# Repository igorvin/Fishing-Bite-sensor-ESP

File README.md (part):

# 🎣 Fishing Bite Sensor

[Русская версия](README_RU.md)

**A wireless bite alarm for fishing rods.** A small sensor on the rod notices even weak line pulls, signals locally with LEDs and a buzzer, and reports the bite over ESP-NOW radio to a **hub**: a receiver with a screen and a vibration motor that stays next to you. No router, Internet or app is needed; all settings open in your phone's browser.

> **Project status.** This is a bench release: the firmware is covered by tests and has run on real XIAO ESP32-C3 boards (sensor + hub), but it **has not been tried on real fishing trips yet**. Bite-detection accuracy, radio range and battery life have not been measured.

## Contents

- [Features](#features)
- [What you need](#what-you-need)
- [Wiring](#wiring)
- [Installing the firmware](#installing-the-firmware)
- [Pairing the sensor with the hub](#pairing-the-sensor-with-the-hub)
- [Web interface](#web-interface)
- [Using it on the water](#using-it-on-the-water)
- [Button, sleep and wake](#button-sleep-and-wake)
- [Signals and states](#signals-and-states)
- [Hub](#hub)
- [Tuning sensitivity](#tuning-sensitivity)
- [Battery](#battery)
- [Troubleshooting](#troubleshooting)
- [For developers](#for-developers)

## Features

**Rod sensor**

- 🎯 **Sensitive detection.** The LSM6DS3 accelerometer is read 104 times per second. The *Dynamic XYZ* algorithm removes gravity and reacts to a jolt in any direction, including across the rod.
- 🔇 **Wind protection.** The sensor reacts to the **sharp** jolt of a bite and ignores the smooth vibration wind gives the rod. The wind level is tracked continuously over the last 10 seconds, so a gust does not raise a false alarm and full sensitivity comes back in calm.
- 🎣 **Pause while handling the rod.** When you pick up or tilt the rod, alarms pause. Once the rod is still again in its **new** position, the sensor re-arms by itself.
- 🔔 **Local signals.** Whenever the sensor is awake (armed or not) the red LED gives a short flash every 5 seconds, so you can tell it from deep sleep, where everything is dark. While armed the green LED is also on. A bite is red LED plus buzzer. Volume is adjustable.
- 📡 **ESP-NOW radio to the hub.** Three events: first bite, continuing bite, low battery.
- 📱 **A simple web page.** The sensor runs its own Wi-Fi access point with a page at `http://192.168.4.1`: state, arming, sensitivity (5 steps), volume. Everything else is in the *Settings* menu.
- 🔘 **One button** for arming, disarming, deep sleep and wake.
- 🔋 **Battery saving.** The sensor sleeps on a button hold or by itself after 3 idle minutes. A brush against the button in a bag does not wake it. Below 3.30 V it also goes to sleep to protect the cell.
- 💾 **Settings are kept** in flash and survive firmware updates.
- 🧾 **Event journal.** The sensor records what it decided and why: button presses, calibrations, arming. Read it over USB with `log`.

**Hub (receiver)**

- 🖥️ 128×64 OLED with a Cyrillic font: the name of the rod that has a bite, in large letters.
- 📳 Vibration motor with different patterns for a bite, a continuing bite and a sensor's low battery.
- 🎣 Up to 8 sensors per hub, log of the last 12 events.
- 🌙 The start-up screen (with the hub MAC) stays on for 20 seconds, then turns off and wakes only for a new alert.
- 🔘 Button: hold 1.5 s to show the hub MAC for pairing, short press for the status screen.

## What you need

| Device | Parts | Notes |
|---|---|---|
| **Sensor** | Seeed XIAO ESP32-C3 (bench) or XIAO ESP32-S3 (PCB v4), LSM6DS3 module (I²C), green and red LEDs, passive buzzer (through a transistor), momentary push button, 3.7 V Li-ion cell, 100 kΩ / 100 kΩ battery divider | A KiCad v4.1 board and an 18650 enclosure are in [`kicad/kicad_bite`](kicad/kicad_bite) |
| **Hub** | XIAO ESP32-C3 or S3, SH1106 128×64 OLED (I²C), vibration motor through a MOSFET, push button, LED, Li-ion cell, 100 kΩ / 100 kΩ divider | Separate firmware in [`ESP_HUB/`](ESP_HUB). Circuit and parts: [docs/hub-hardware.md](docs/hub-hardware.md) (Russian) |
| **Phone** | Any smartphone with Wi-Fi and a browser | Only for configuration |
| **Computer** | [PlatformIO](https://platformio.org/install), USB-C cable | For flashing |

<p align="center">
  
  <br><em>Concept: the sensor in a compact case, strapped to the rod with hook-and-loop straps.</em>
</p>

<p align="center">

  <br><em>PCB v4.1 and the sealed tube enclosure for an 18650 cell (design files; not yet built or tested).</em>
</p>

## Wiring

### Sensor — bench (XIAO ESP32-C3 / S3)

| Signal | XIAO pin | Notes |
|---|---|---|
| Button | **D1** | To GND; internal pull-up |
| Battery (100k/100k divider) | D2 | |
| LSM6DS3 SDA / SCL | D4 / D5 | Module powered from 3.3 V |
| Green LED | D7 | Through a resistor or driver |
| Red LED | D8 | Through a resistor or driver |
| Passive buzzer | D9 | Through a transistor; 3 kHz PWM |

The button must be on **D1**: the board cannot wake from deep sleep on D6. D0 and D6 are unused by the current firmware.

### Sensor — Waveshare ESP32-S3-Zero (environment `s3_zero`)

This board labels its pins by GPIO number (GP1…GP13), not D0…D10, so the wiring is given in GPIO numbers:

| Signal | GPIO | Notes |
|---|---|---|
| LSM6DS3 SDA / SCL | GP4 / GP5 | Module powered from 3.3 V |
| Button (to GND) | GP6 | Wakes from deep sleep; internal pull-up |
| Battery (100k/100k divider) | GP7 | |
| Green LED | GP8 | |
| Red LED | GP9 | |
| Passive buzzer (through a transistor) | GP10 | 3 kHz PWM |

Do not use GP0 (BOOT button), GP3 (affects boot), GP21 (on-board RGB LED), GP19/GP20 (USB) or TX/RX (GP43/GP44). **The ESP32-S3-Zero has no battery charger or BAT pads:** connect a Li-ion cell through a separate charge/protection module to the 5V pin and take the divider from the cell. Check against Waveshare's schematic for your board revision: the pinout above is verified by building the firmware only, not on the board itself.

### Sensor — PCB v4 (XIAO ESP32-S3, environment `bite_v4_s3`)

Button D1 (external 10k pull-up), battery D0, red LED D8, green LED D9, buzzer D10, LSM6DS3 on D4/D5.

### Hub

| Signal | XIAO pin | Waveshare ESP32-S3-Zero (`s3_zero`) |
|---|---|---|
| OLED SDA / SCL | D4 / D5 | GP4 / GP5 |
| LED | D1 | GP8 |
| Motor MOSFET | D2 | GP9 |
| Button (to GND) | D3 | GP6 |
| Battery (100k/100k divider) | A0 | GP7 |

Choosing and wiring the vibration motor, with the parts list: [docs/hub-hardware.md](docs/hub-hardware.md) (Russian). In short: an AO3400A MOSFET with 100 Ω gate resistor and 100 kΩ gate pull-down, an SS14 flyback diode across the motor, 10 µF + 100 nF on the motor supply, motor powered from 3V3.

> ⚠️ Drive the motor and any loud buzzer through a transistor, never straight from a pin. Connect the Li-ion cell to the XIAO **BAT+ / BAT−** pads, not to 3V3. Power details: [docs/power-and-wiring.md](docs/power-and-wiring.md).

## Installing the firmware

1. **Install PlatformIO**, either [PlatformIO IDE for VS Code](https://platformio.org/install/ide?install=vscode) or the [PlatformIO Core CLI](https://docs.platformio.org/en/latest/core/installation/index.html). Make sure `pio --version` works.

2. **Get the project.**

   ```bash
   git clone https://github.com/igorvin/Fishing-Bite-sensor-ESP.git
   ```

   ```bash
   cd Fishing-Bite-sensor-ESP
   ```

3. **Flash the sensor.** Connect the sensor board over USB and pick the environment for your board. `<PORT>` is the board's port, e.g. `/dev/ttyACM0` or `COM5`.

   | Board | Environment |
   |---|---|
   | XIAO ESP32-C3 (bench) | `xiao_esp32c3` |
   | XIAO ESP32-S3 (bench) | `seeed_xiao_esp32s3` |
   | PCB v4 (XIAO ESP32-S3) | `bite_v4_s3` |
   | Waveshare ESP32-S3-Zero | `s3_zero` |

   ```bash
   pio run -e xiao_esp32c3 -t upload --upload-port <PORT>
   ```

4. **Flash the hub.** Connect the **other** board, the hub, and run:

   ```bash
   pio run -d ESP_HUB -e xiao_esp32c3 -t upload --upload-port <PORT>
   ```

   For a XIAO ESP32-S3 use `-e seeed_xiao_esp32s3`, for a Waveshare ESP32-S3-Zero `-e s3_zero`.

> 💡 Mind the ports: hub firmware on the sensor (or the other way round) will not work. For an ordinary update **do not** run `erase_flash` or `uploadfs`; they wipe the saved settings.

## Pairing the sensor with the hub

The sensor sends events only to the hub whose MAC address you give it.

1. **Find the hub's MAC.** It is on the bottom line of the start-up screen for 20 seconds after the hub is switched on. Holding the hub button for 1.5 seconds shows it in large digits for 30 seconds. Over USB: type `mac` in the hub's serial monitor.

   ```bash
   pio device monitor -d ESP_HUB --port <PORT> --baud 115200
   ```

2. **Give the MAC to the sensor**, in either of two ways:
   - **From the phone:** open the *Settings* menu, type the MAC into "Hub MAC" and press **"Save and restart"**. A filled-in MAC turns the hub link on by itself.
   - **Over USB:** in the sensor's serial monitor type `peer AA:BB:CC:DD:EE:FF` (the sensor must be disarmed).

3. **Check the link.** After the restart the sensor introduces itself to the hub. The sensor's page shows "Answered at power-on" in the Hub row, and the `status` command in the hub's serial monitor shows `rods=1`. Start-up order does not matter: if you restart the hub, a running sensor registers again.

> ℹ️ Registration is a one-off hello at start-up, not a continuous link check. Individual bites are not acknowledged. Before fishing, check that an alarm reaches the hub: arm the sensor and tap the rod.

## Web interface

1. Power on the sensor (or wake it by holding the button for about 1 s).
2. On your phone join the Wi-Fi network **`BiteSensor`** (the name on first start; no password).
3. Open **http://192.168.4.1** in the browser.

Everything fits on one page; the rarely used fields are in the **Settings** menu. Changes are saved at once; when something goes wrong (for example an ARM is cancelled) a pop-up message appears.

<table>
<tr>
<td align="center" width="50%"><br><b>Main page</b></td>
<td align="center" width="50%"><br><b>Settings</b></td>
</tr>
</table>

<sub>Pictures are taken from the firmware's real web front end (Settings library 1.4.3) with example values.</sub>

### Main page

| Item | What it shows or does |
|---|---|
| **State** | Off / Arming… / ARMED / Paused: rod is being moved / Calibrating… / Sensor error |
| **Battery** | Approximate charge in percent; "no reading" on USB power only |
| **Hub** | "Not set up" (enter its MAC) / "Waiting for the hub" / "Answered at power-on" / "Radio error" |
| **Armed** | Arms or disarms, like the button |
| **Sensitivity** | 5 steps, "High" by default (see below) |
| **Volume** | Buzzer volume, 0–100 % |
| **Test signal** | A short buzzer and red-LED signal. Nothing is sent to the hub |

| Sensitivity | Sharpness floor | Threshold in wind |
|---|---|---|
| Low | 0.030 g | wind level × 10 |
| Below medium | 0.022 g | × 8 |
| Medium | 0.016 g | × 7 |
| **High** (default) | 0.012 g | × 6 |
| Very high | 0.009 g | × 5 |

### Settings menu

| Setting | Description |
|---|---|
| **Rod name** | The sensor's Wi-Fi name and the name on the hub screen; the hub shows the first 16 bytes (16 Latin letters). Give each sensor its own name, e.g. "Feeder", "Carp-1" |
| **Wi-Fi password** | Empty (open) or 8–63 characters |
| **Hub MAC** | The hub's MAC as `AA:BB:CC:DD:EE:FF`. Empty means the hub link is off |
| **Save and restart** | Applies the three fields above. They have no effect until you press it |
| **Language / Язык** | English or Русский |

Everything else (signal timings, the movement pause with its 25° / 35° limits, LED brightness 100 %) runs on tested defaults. Technical data, the journal and raw capture are available over USB (see [USB commands](#troubleshooting)).

## Using it on the water

1. **Power on or wake the sensor.** Hold the button for about 1 second until it beeps. The sensor measures the background straight away, so **keep it still for 2 seconds**.
2. **Mount the sensor on the rod** and put the rod on its rest.
3. **Arm.** Hold the button for 1–3 seconds: a short beep sounds at 1 second, then release. The **green LED blinks** while the sensor checks for 1.5 seconds that it is *steady* (*SETTLING*): swaying in wind is fine, being handled or moved is not and restarts the check. When the green LED stays on and a **long beep** sounds, it is armed. Do not press again while green is blinking: a second press disarms. If the sensor has not been calibrated yet, it starts calibrating 1 second after you release the button (do not touch it for 2 seconds).
4. **Bite:** red LED and buzzer on the sensor, screen and vibration on the hub. The signal repeats while the line keeps moving.
5. **Picked up the rod?** No need to disarm: the sensor pauses alarms and re-arms by itself once the rod is still again, in its new position.
6. **Disarm** with the same 1–3 second hold: the green LED goes out and you hear a short beep.
7. **Sleep.** Hold the button for more than 3 seconds (long beep) and release. A disarmed sensor with nobody connected also falls asleep after 3 minutes.

> 💡 While armed, the sensor's Wi-Fi stays on for 2 more minutes and then switches off to save power. To open the settings again, disarm with the button; the access point comes back.

## Button, sleep and wake

| Action | Result |
|---|---|
| Hold 1–3 s and release | Short beep at 1 s; on release the sensor arms or disarms. If not calibrated, calibration starts 1 s after release |
| Hold ≥ 3 s and release | Long beep at 3 s; on release it disarms, saves settings and sleeps |
| Touch < 1 s while asleep | Nothing: it goes straight back to sleep (protection against presses in a bag) |
| Hold ≈ 1 s while asleep | Beep, wake, calibration, DISARMED. The sensor registers with the hub again |
| 3 min disarmed with no presses or connections | Sleep |
| Battery < 3.30 V (three readings in a row) | If armed, the hub gets "low battery"; then the sensor sleeps |

## Signals and states

| Situation | Green | Red | Buzzer | Hub |
|---|---|---|---|---|
| Awake, disarmed | — | short flash every 5 s | short beep when disarming | — |
| Arming (SETTLING) | blinking | short flash every 5 s | — | — |
| Armed | on | short flash every 5 s | long beep when ARMED is reached | — |
| Deep sleep | — | — | — | — |
| **ARM cancelled**: the sensor moved during calibration | — | 3 flashes | 3 short beeps | — |
| Bite (event 1) | on | flash | short signal | screen + 300 ms vibration |
| Continuing bite (event 2) | on | repeated flashes | repeated signals | 800 ms vibration at the start of the episode |
| Rod being moved (pause) | — | — | silent | — |
| Battery ≤ 20 % while armed (event 3) | | | | screen + 2 short vibrations |
| Holding the button | | | beep at 1 s, long beep at 3 s | |

```mermaid
stateDiagram-v2
    direction LR
    state "Calibrating" as Cal
    state "Disarmed" as Off
    state "Settling" as Settle
    state "Armed" as Armed
    state "Suppressed (moving)" as Pause
    state "IMU fault" as Fault
    [*] --> Cal: power on
    Cal --> Off: 2 s still
    Off --> Settle: ARM
    Settle --> Armed: 1.5 s still
    Armed --> Armed: bite → signal
    Armed --> Pause: rod tilted
    Pause --> Settle: still again
    Armed --> Off: DISARM
    Pause --> Off: DISARM
    Armed --> Fault: accelerometer lost
    Fault --> Cal: accelerometer back
```

An accelerometer fault or a manual disarm **never** re-arms the sensor by itself; you arm it again yourself.

## Hub

After power-on the hub shows for about 20 seconds how many sensors it has seen, its own battery and, on the bottom line, **its MAC address** for pairing; then the screen turns off. A new bite or battery warning turns on the screen and the motor.

<table>
<tr>
<td align="center"><br>Ready to receive</td>
<td align="center"><br>Bite on rod "ФИДЕР"</td>
</tr>
<tr>
<td align="center"><br>Sensor battery low</td>
<td align="center"><br>Event log (USB command)</td>
</tr>
</table>

<sub>Frames are produced by the hub's own drawing code (`ESP_HUB/tools/render_preview.py`) with example names. The hub's interface is in Russian.</sub>

**Hub button (D3):** hold 1.5 s for the hub MAC (30 seconds); short press for the status screen (another short press turns the screen off). Alerts always take priority.

- Rod numbers (01, 02, …) follow the order in which sensors first appear after the hub starts. After a hub restart the list and log start empty.
- List, log and service screens open with serial commands: `summary`, `list`, `history`, `service`, `mac`, `status`, `help`. `motor` runs the motor for 300 ms as a wiring test.
- More: [ESP_HUB/README.md](ESP_HUB/README.md), [docs/hub-testing.md](docs/hub-testing.md).

## Tuning sensitivity

1. Start with **High**.
2. Arm and tap the rod blank lightly or pull the line. If nothing happens, choose **Very high**.
3. Leave the rod on its rest for a few minutes, ideally in the wind. If false alarms appear, go one step lower.
4. The current threshold and wind level are shown over USB: `status` (`ambient`, `threshold`) and the journal line `ARMED: ambient … -> threshold …`.

### Wind and a swaying rod

Wind recordings (`docs/field-analysis-2026-11-24.md`) showed the wind shaking the rod about 5 times a second by ±0.2–0.3 g, while a bite is a short sharp jolt ringing at 15–30 Hz. So the sensor looks at **sharpness**: a filter removes everything slower than ~12 Hz, and the floor and multiplier come from the sensitivity step. The background level is the median sharpness over the last ~10 seconds (excluding the latest second), refreshed every half second in every state.

On the same recordings, through the firmware core, at "High": in strong wind the sensor arms and stays armed with no false alarm, catches 33 of 35 light simulated bites in calm and 19 of 24 taps in wind. Before: 35 false alarms a minute and 12 of 35.

Arming does not need complete stillness. A 1.5 s window is checked for **steadiness**:

| Check | Limit | Means |
|---|---|---|
| Position drift (first vs second half of the window) | 0.035 g (≈2°) | the rod is being moved to a new place |
| Peak-to-peak jolt on any axis | 0.20 g; in strong sway up to 6 × sway, never above 0.80 g | the sensor is being handled |
| Sway (standard deviation) | 0.15 g | wind too strong |

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
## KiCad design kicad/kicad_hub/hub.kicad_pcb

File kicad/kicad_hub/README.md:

# Плата и корпус хаба (плата rev A, корпус rev B; черновик, 2026-11-27)

Плата 68 × 40 мм под XIAO ESP32-C3, модуль OLED SH1106 1,3″, вибромотор, кнопку и тонкий LiPo 703048 (48 × 30 × 7 мм, ~1000 мА·ч) с быстрой зарядкой BQ24074. Корпус «бипер» 72 × 44 × 19 мм со скруглёнными углами и рёбрами и откидной клипсой: сложенная держит хаб на ремне, откинутая служит подставкой на столе (с клипсой толщина ~24 мм).

Корпус rev B (2026-11-27, по просьбе сделать тоньше и эстетичнее): был 75 × 47 × 24 (30 с клипсой) под LiPo 10 мм. Тоньше за счёт аккумулятора 7 мм вместо 10, зазора над ним 1 мм вместо 2, гребёнки OLED 3,0 мм вместо 3,5 и более тонких крышки и лицевой стенки. Угловые винты убраны, поэтому углы скруглены R ≈ 3,7 мм в плане, лицевое ребро R 3, заднее R 1,2. Плата не менялась.

**Статус:** проект собран генератором и проверен программно (нетлист, DRC, проверка посадки в корпусе). Ничего не заказано и не собрано. Перед заказом надо сверить с даташитами пункты из раздела «Проверить до заказа».

| | |
|---|---|
|  |  |
|  |  |

## Файлы

| Файл | Что это |
|---|---|
| `hub.kicad_sch`, `hub_schematic.pdf`, `docs/img/schematic-1.png` | схема (формат KiCad 7, открывается в KiCad 8/9) |
| `hub.kicad_pcb` | разведённая плата, 2 слоя, 1,0 мм, заливка GND с обеих сторон |
| `hub.pretty`, `hub.kicad_sym` | свои посадочные места (XIAO, OLED на гребёнке, площадки мотора) и символ XIAO ESP32-C3 |
| `fab/hub_gerbers.zip` | Gerber + сверловка для заказа платы |
| `fab/hub-bom.csv`, `fab/hub-pos.csv` | перечень деталей и координаты для монтажа |
| `fab/hub.step` | 3D-модель платы (детали без моделей — только площадки) |
| `docs/drc_report.txt` | DRC: 0 ошибок, 0 неразведённых; 2 предупреждения — шёлкография библиотечного SW1 выходит за край (так задумано: рычажок свешивается) |
| `enclosure/hub_enclosure.scad` | параметрическая модель корпуса (OpenSCAD), размеры в начале файла |
| `enclosure/stl/*.stl` | детали для печати |
| `_generator/` | генератор: схема → плата → Freerouting → заливка → DRC → файлы производства |

## Схема

Питание: **USB-C J1 → F1/VD1 → BQ24074 → SYS → выключатель SW1 → диод D3 → вывод 5V XIAO → стабилизатор XIAO 3,3 В** → OLED, мотор, светодиод.

- **Зарядка BQ24074:** ток заряда ≈ 0,59 А (R3 = 1,5 кОм, ≈ 0,6C для 703048 ~1000 мА·ч, полная зарядка ≈ 2–2,5 ч; если паспорт аккумулятора разрешает меньше, увеличить R3), входной ток ≈ 1 А (R4 = 1,5 кОм). Power-path: от USB хаб работает и во время зарядки. TS — резистор 10 кОм вместо NTC (температура аккумулятора не контролируется). Светодиоды: красный D1 «заряжается», зелёный D2 «USB подключён», видны через глухие окна в корпусе.
- **USB-C J1** — только питание (CC1/CC2 через 5,1 кОм), данных нет. Прошивка — через USB-C самой XIAO на верхнем торце.
- **Аккумулятор** — разъём JST-PH 2P J2 снизу платы. Q1 (AO3401A) защищает от разъёма с обратной полярностью (у китайских LiPo она встречается). **Аккумулятор должен быть со своей платой защиты**: отдельной защиты от переразряда на плате нет.
- **SW1** разрывает питание XIAO, зарядка работает и при выключенном хабе. **D3** не даёт USB XIAO питать зарядник в обратную сторону, поэтому оба USB можно подключать одновременно (проверить на первом образце).
- **Выводы как в прошивке `ESP_HUB`** (ничего менять не нужно): светодиод D1, мотор D2 (AO3400A, диод D4, 10 мкФ + 100 нФ), кнопка D3 к GND, OLED D4/D5 (подтяжки 4,7 кОм), делитель батареи 100k/100k на A0.

## Корпус

| Деталь | Материал / печать |
|---|---|
| `shell.stl` — оболочка с экраном | **полупрозрачный (натуральный) или белый PETG**: светодиоды светят через глухие окна 0,6 мм. Печать экраном вниз |
| `cover.stl` — задняя крышка с рамкой аккумулятора, кольцом мотора и петлями клипсы | PETG, наружной стороной вниз |
| `clip.stl` — клипса/подставка | PETG (гнётся без излома), на боку |
| `pusher.stl` — толкатель кнопки | PETG |
| `flap.stl` — заглушка USB-C зарядки и выключателя | **ТПУ 85–95A** |
| `plug_top.stl` — пробка USB-C XIAO | ТПУ |
| `gasket.stl` — плоская прокладка крышки 0,8 мм | ТПУ 85A |

Защита от воды «от дождя и брызг»: прокладка по шву крышки, толкатель кнопки с O-кольцом 2,5 × 1,0 в отверстии Ø4,1, окно экрана — пластина 34,6 × 20,6 × 1 мм (акрил или поликарбонат) вклеена изнутри на силикон, светодиоды без отверстий, оба USB-C под ТПУ-заглушками. Погружение не предусмотрено.

Клипса крепится винтом M2 × 40–45 (или отрезком прутка 2 мм) через три петли с самоконтрящейся гайкой: затяжкой регулируется, насколько туго она откидывается. Сложенная, она оставляет под ремень зазор 3,0 мм с зацепом на конце. Откинутая примерно на 42°, она упирается выступом в крышку и держит хаб на столе.

Сборка: четыре самореза M2 × 14 вставляются сзади через крышку, её стойки и крепёжные отверстия платы и вкручиваются в бобышки оболочки (пилот Ø1,8). Так одни винты держат и плату, и крышку, а углы свободны для скругления. Аккумулятор лежит в рамке крышки между рядами стоек; над ним до платы 1 мм, поэтому выводы THT-деталей снизу платы обрезать заподлицо и проложить каптон.

## Предположения (уточнить, сейчас не измерено)

1. **LiPo 703048: 48 × 30 × 7 мм, ~1000 мА·ч** (размеры по типовой маркировке, с платой защиты и выводами JST-PH). Вариант тоньше — 603048 (6 мм, ~850 мА·ч, корпус 18 мм). Размер задаётся параметром `BAT` в `.scad`; ширина больше 30 мм не пройдёт между стойками винтов.
2. **Модуль OLED 1,3″ 35,4 × 33,5 мм, выводы GND-VCC-SCL-SDA** на верхнем краю. Бывают модули с VCC и GND наоборот — тогда плату нужно поменять (или резать дорожки). Окно `WIN` 31 × 17 мм по центру модуля — сверить с реальным стеклом.
3. Модуль OLED стоит над платой на гребёнке с зазором 3,0 мм; детали под ним не выше 1,0 мм.
4. Ток хаба не измерен; ~1000 мА·ч по оценке хватит на 12–15 ч.

## Проверить до заказа

- BQ24074: формулы ISET/ILIM (K_ISET = 890, K_ILIM = 1550 взяты по памяти), назначение вывода 15 (SYSOFF у BQ24074; R6 0 Ом на GND, при необходимости не ставить), таймер TMR оставлен свободным.
- Посадочное место XIAO (`hub:XIAO_THT`) — по чертежу Seeed: 14 площадок, шаг 2,54, ряды 15,24 мм.
- Полярность разъёма аккумулятора: 1 = «+» (по маркировке на нижнем слое).
- Ориентация JST J2 и SW1 на реальных деталях, вылет рычажка SW1 за край платы (~1 мм).

## Пересборка

```sh
# Linux (Ubuntu 24.04): apt install kicad kicad-symbols kicad-footprints openscad xvfb
bash kicad/kicad_hub/_generator/run_hub.sh        # схема, плата, трассировка, DRC, Gerber, BOM (~3 мин)
bash kicad/kicad_hub/enclosure/build.sh           # STL, картинки, проверка посадки (~1 мин)
```

На macOS с KiCad 8/9 задать `KPY` и `KICAD_CLI` (см. начало `run_hub.sh`). Freerouting 2.1 скачивается сам. Трассировщик не детерминирован: скрипт повторяет трассировку, пока DRC не покажет 0 неразведённых площадок, поэтому дорожки при каждой пересборке немного разные.

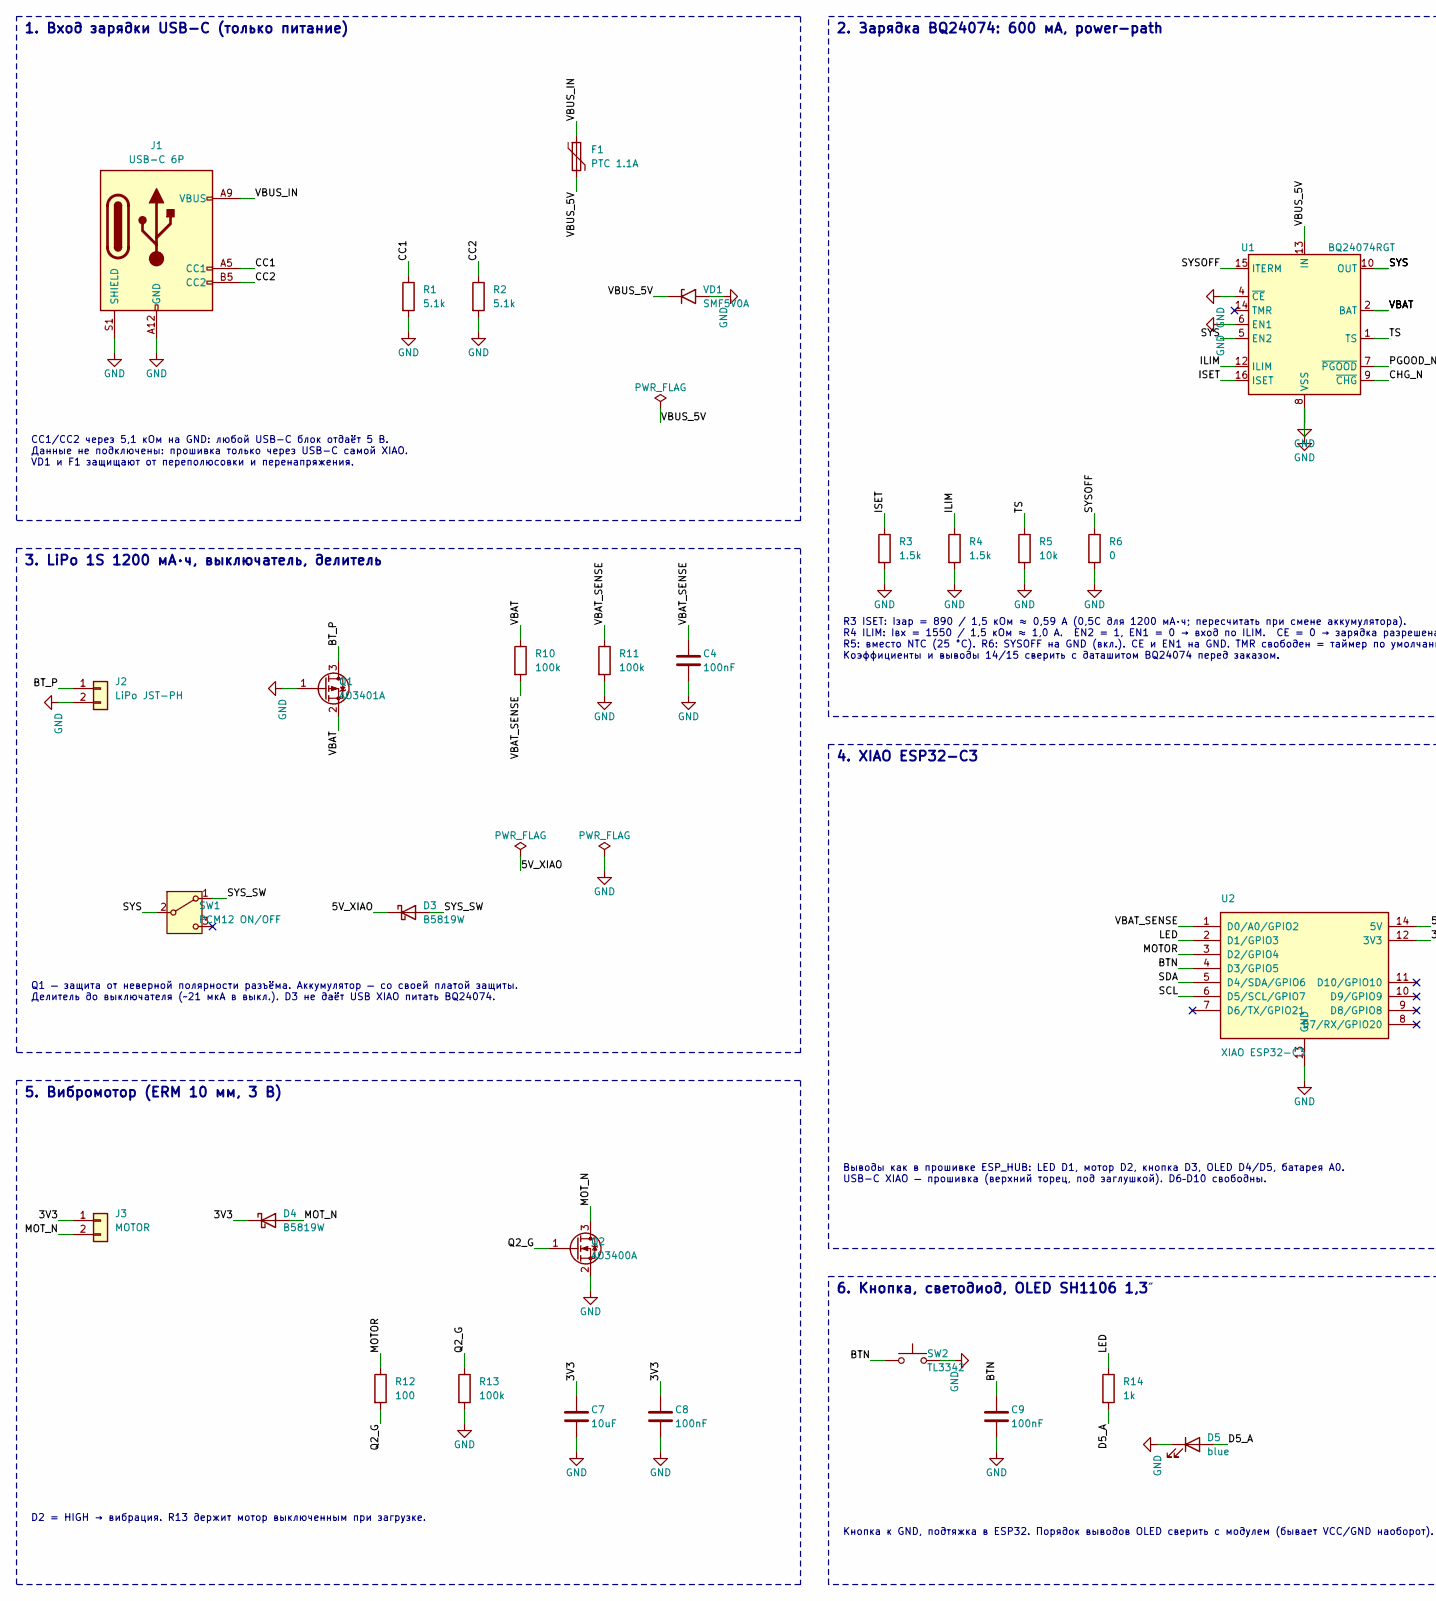
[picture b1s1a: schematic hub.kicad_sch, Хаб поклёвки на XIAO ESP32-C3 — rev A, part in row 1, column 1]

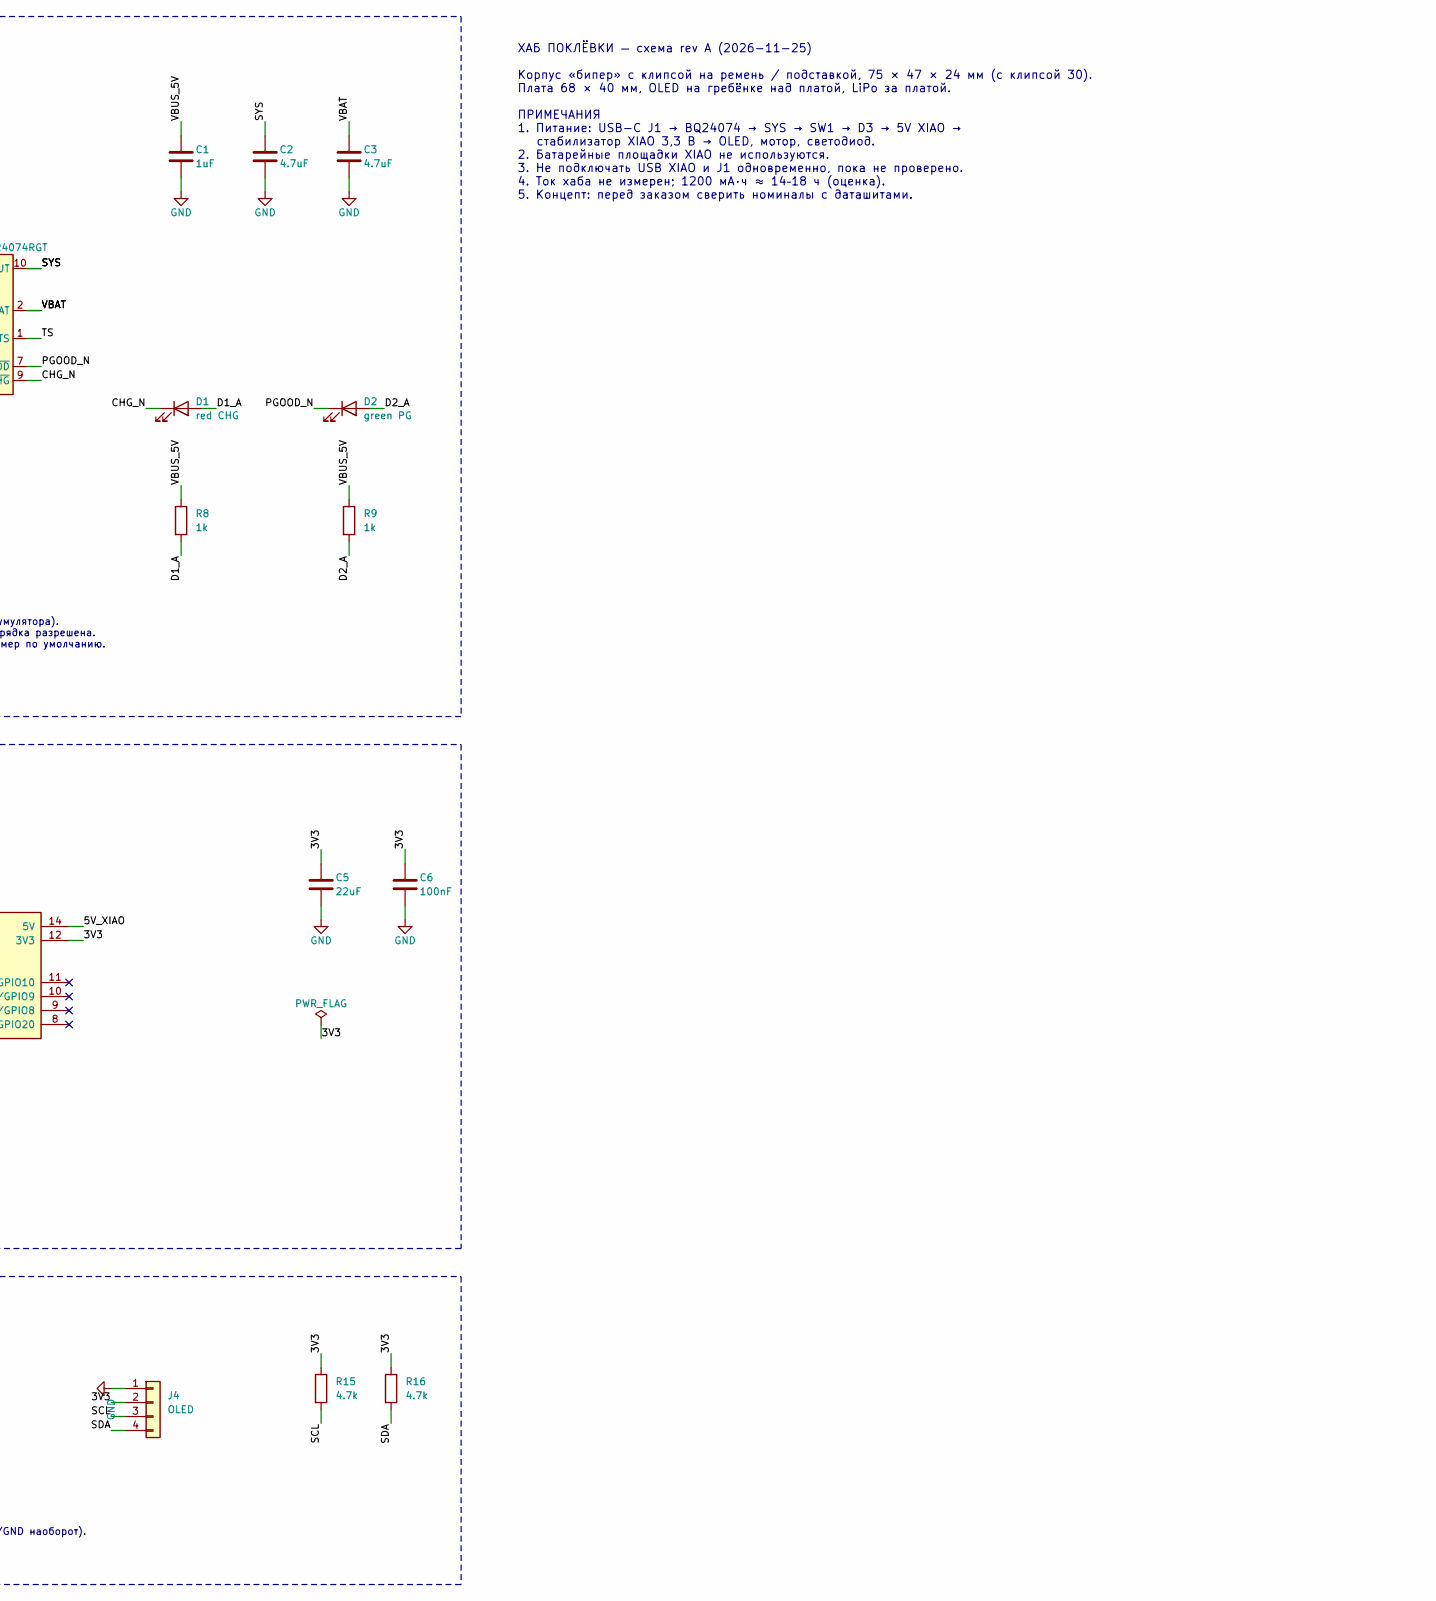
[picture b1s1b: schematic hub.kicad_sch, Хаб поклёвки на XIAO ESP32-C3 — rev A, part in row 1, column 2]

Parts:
C1: 1uF; C_0805_2012Metric
C2, C3: 4.7uF; C_0805_2012Metric
C4, C6, C8, C9: 100nF; C_0603_1608Metric
C5: 22uF; C_0805_2012Metric
C7: 10uF; C_0805_2012Metric
D1: red CHG; LED_0603_1608Metric
D2: green PG; LED_0603_1608Metric
D3, D4: B5819W; D_SOD-123
D5: blue; LED_0603_1608Metric
F1: PTC 1.1A; Fuse_1206_3216Metric; MPN Bourns MF-NSMF110-2
J1: USB-C 6P; USB_C_Receptacle_GCT_USB4125-xx-x-0190_6P_TopMnt_Horizontal; MPN GCT USB4125-GF-A-0190
J2: LiPo JST-PH; JST_PH_S2B-PH-SM4-TB_1x02-1MP_P2.00mm_Horizontal; MPN JST S2B-PH-SM4-TB
J3: MOTOR; WIRE_2P
J4: OLED; PinHeader_1x04_P2.54mm_Vertical
Q1: AO3401A; SOT-23
Q2: AO3400A; SOT-23
R1, R2: 5.1k; R_0603_1608Metric
R3, R4: 1.5k; R_0603_1608Metric
R5: 10k; R_0603_1608Metric
R6: 0; R_0603_1608Metric
R8, R9, R14: 1k; R_0603_1608Metric
R10, R11, R13: 100k; R_0603_1608Metric
R12: 100; R_0603_1608Metric
R15, R16: 4.7k; R_0603_1608Metric
SW1: PCM12 ON/OFF; SW_SPDT_PCM12; MPN C&K PCM12SMTR
SW2: TL3342; SW_SPST_TL3342; MPN E-Switch TL3342F160QG
U1: BQ24074RGT; VQFN-16-1EP_3x3mm_P0.5mm_EP1.6x1.6mm; MPN TI BQ24074RGTR
U2: XIAO ESP32-C3; XIAO_THT; MPN Seeed 113991054
VD1: SMF5V0A; D_SMF

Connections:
/3V3: C5.1, C6.1, C7.1, C8.1, D4.1 (K), J3.1, J4.2, R15.1, R16.1, U2.12 (3V3)
/5V_XIAO: D3.1 (K), U2.14 (5V)
/BTN: C9.1, SW2.1, U2.4 (D3/GPIO5)
/BT_P: J2.1, Q1.3 (D)
/CC1: J1.A5 (CC1), R1.1
/CC2: J1.B5 (CC2), R2.1
/CHG_N: D1.1 (K), U1.9 (~CHG)
/D1_A: D1.2 (A), R8.2
/D2_A: D2.2 (A), R9.2
/D5_A: D5.2 (A), R14.2
/ILIM: R4.1, U1.12 (ILIM)
/ISET: R3.1, U1.16 (ISET)
/LED: R14.1, U2.2 (D1/GPIO3)
/MOTOR: R12.1, U2.3 (D2/GPIO4)
/MOT_N: D4.2 (A), J3.2, Q2.3 (D)
/PGOOD_N: D2.1 (K), U1.7 (~PGOOD)
/Q2_G: Q2.1 (G), R12.2, R13.1
/SCL: J4.3, R15.2, U2.6 (D5/SCL/GPIO7)
/SDA: J4.4, R16.2, U2.5 (D4/SDA/GPIO6)
/SYS: C2.1, SW1.2 (B), U1.5 (EN2), U1.10 (OUT), U1.11 (OUT)
/SYSOFF: R6.1, U1.15 (ITERM)
/SYS_SW: D3.2 (A), SW1.1 (A)
/TS: R5.1, U1.1 (TS)
/VBAT: C3.1, Q1.2 (S), R10.1, U1.2 (BAT), U1.3 (BAT)
/VBAT_SENSE: C4.1, R10.2, R11.1, U2.1 (D0/A0/GPIO2)
/VBUS_5V: C1.1, F1.2, R8.1, R9.1, U1.13 (IN), VD1.1 (A1)
/VBUS_IN: F1.1, J1.A9 (VBUS), J1.B9 (VBUS)
GND: C1.2, C2.2, C3.2, C4.2, C5.2, C6.2, C7.2, C8.2, C9.2, D5.1 (K), J1.A12 (GND), J1.B12 (GND), J1.S1 (SHIELD), J2.2, J4.1, Q1.1 (G), Q2.2 (S), R1.2, R2.2, R3.2, R4.2, R5.2, R6.2, R11.2, R13.2, SW2.2, U1.4 (~CE), U1.6 (EN1), U1.8 (VSS), U1.17 (VSS), U2.13 (GND), VD1.2 (A2)

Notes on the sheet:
1. Вход зарядки USB-C (только питание)
CC1/CC2 через 5,1 кОм на GND: любой USB-C блок отдаёт 5 В. Данные не подключены: прошивка только через USB-C самой XIAO. VD1 и F1 защищают от переполюсовки и перенапряжения.
2. Зарядка BQ24074: 600 мА, power-path
R3 ISET: Iзар = 890 / 1,5 кОм ≈ 0,59 А (0,5C для 1200 мА·ч; пересчитать при смене аккумулятора). R4 ILIM: Iвх = 1550 / 1,5 кОм ≈ 1,0 А. EN2 = 1, EN1 = 0 → вход по ILIM. CE = 0 → зарядка разрешена. R5: вместо NTC (25 °C). R6: SYSOFF на GND (вкл.). CE и EN1 на GND. TMR свободен = таймер по умолчанию.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
3. LiPo 1S 1200 мА·ч, выключатель, делитель
Q1 — защита от неверной полярности разъёма. Аккумулятор — со своей платой защиты. Делитель до выключателя (~21 мкА в выкл.). D3 не даёт USB XIAO питать BQ24074.
4. XIAO ESP32-C3
Выводы как в прошивке ESP_HUB: LED D1, мотор D2, кнопка D3, OLED D4/D5, батарея A0. USB-C XIAO — прошивка (верхний торец, под заглушкой). D6–D10 свободны.
5. Вибромотор (ERM 10 мм, 3 В)
D2 = HIGH → вибрация. R13 держит мотор выключенным при загрузке.
6. Кнопка, светодиод, OLED SH1106 1,3″
Кнопка к GND, подтяжка в ESP32. Порядок выводов OLED сверить с модулем (бывает VCC/GND наоборот).
ХАБ ПОКЛЁВКИ — схема rev A (2026-11-25) Корпус «бипер» с клипсой на ремень / подставкой, 75 × 47 × 24 мм (с клипсой 30). Плата 68 × 40 мм, OLED на гребёнке над платой, LiPo за платой. ПРИМЕЧАНИЯ 1. Питание: USB-C J1 → BQ24074 → SYS → SW1 → D3 → 5V XIAO → стабилизатор XIAO 3,3 В → OLED, мотор, свето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

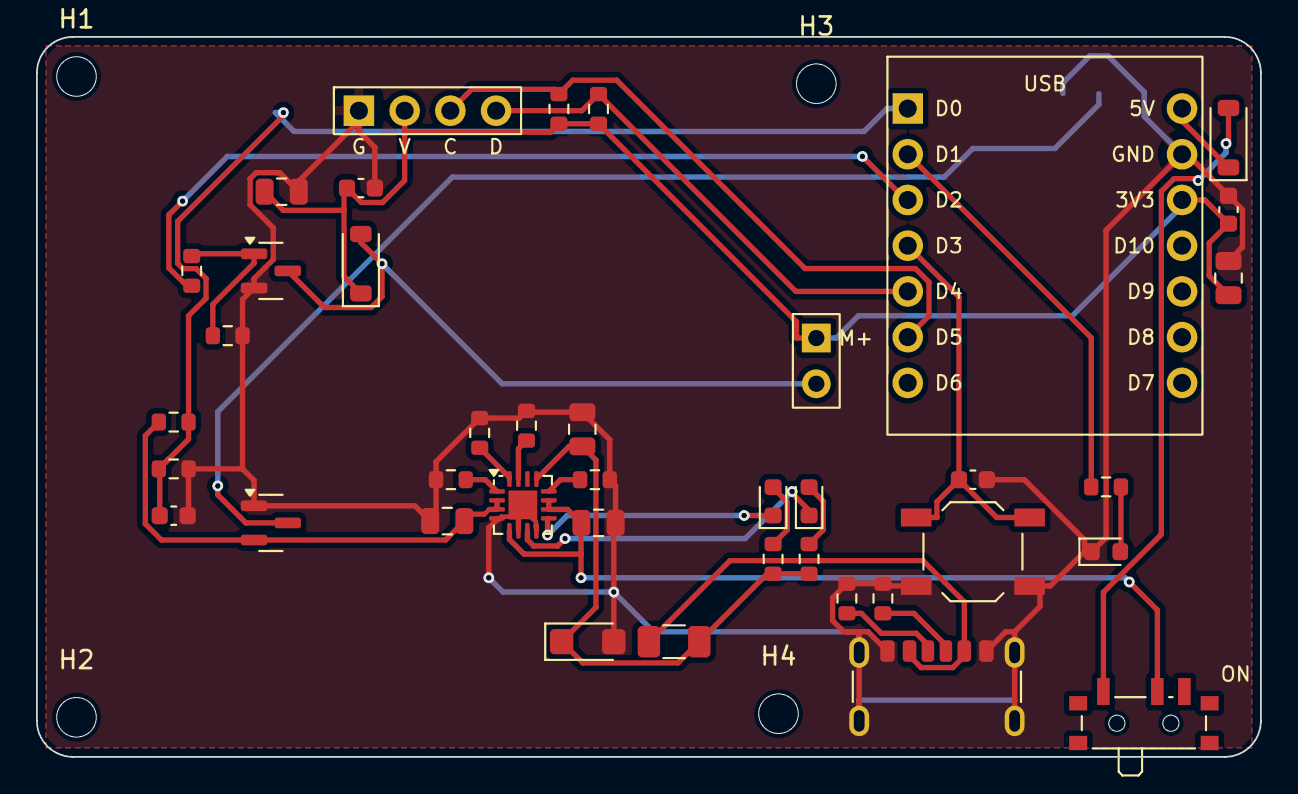
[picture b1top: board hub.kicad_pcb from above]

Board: 2 copper layers, 68.0 x 40.0 mm, 45 parts (1 on the bottom side), 28 nets.

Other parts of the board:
H1, H2, H3, H4: MountingHole_2.2mm_M2

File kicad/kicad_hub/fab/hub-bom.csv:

Qty,References,Value,Footprint,MPN / note
1,C1,1uF,C_0805_2012Metric,
2,C2 C3,4.7uF,C_0805_2012Metric,
4,C4 C6 C8 C9,100nF,C_0603_1608Metric,
1,C5,22uF,C_0805_2012Metric,
1,C7,10uF,C_0805_2012Metric,
1,D1,red CHG,LED_0603_1608Metric,
1,D2,green PG,LED_0603_1608Metric,
2,D3 D4,B5819W,D_SOD-123,
1,D5,blue,LED_0603_1608Metric,
1,F1,PTC 1.1A,Fuse_1206_3216Metric,Bourns MF-NSMF110-2
1,J1,USB-C 6P,USB_C_Receptacle_GCT_USB4125-xx-x-0190_6P_TopMnt_Horizontal,GCT USB4125-GF-A-0190
1,J2,LiPo JST-PH,JST_PH_S2B-PH-SM4-TB_1x02-1MP_P2.00mm_Horizontal,JST S2B-PH-SM4-TB
1,J3,MOTOR,WIRE_2P,
1,J4,OLED,PinHeader_1x04_P2.54mm_Vertical,
1,Q1,AO3401A,SOT-23,
1,Q2,AO3400A,SOT-23,
2,R1 R2,5.1k,R_0603_1608Metric,
2,R3 R4,1.5k,R_0603_1608Metric,
1,R5,10k,R_0603_1608Metric,
1,R6,0,R_0603_1608Metric,
3,R8 R9 R14,1k,R_0603_1608Metric,
3,R10 R11 R13,100k,R_0603_1608Metric,
1,R12,100,R_0603_1608Metric,
2,R15 R16,4.7k,R_0603_1608Metric,
1,SW1,PCM12 ON/OFF,SW_SPDT_PCM12,C&K PCM12SMTR
1,SW2,TL3342,SW_SPST_TL3342,E-Switch TL3342F160QG
1,U1,BQ24074RGT,VQFN-16-1EP_3x3mm_P0.5mm_EP1.6x1.6mm,TI BQ24074RGTR
1,U2,XIAO ESP32-C3,XIAO_THT,Seeed 113991054
1,VD1,SMF5V0A,D_SMF,

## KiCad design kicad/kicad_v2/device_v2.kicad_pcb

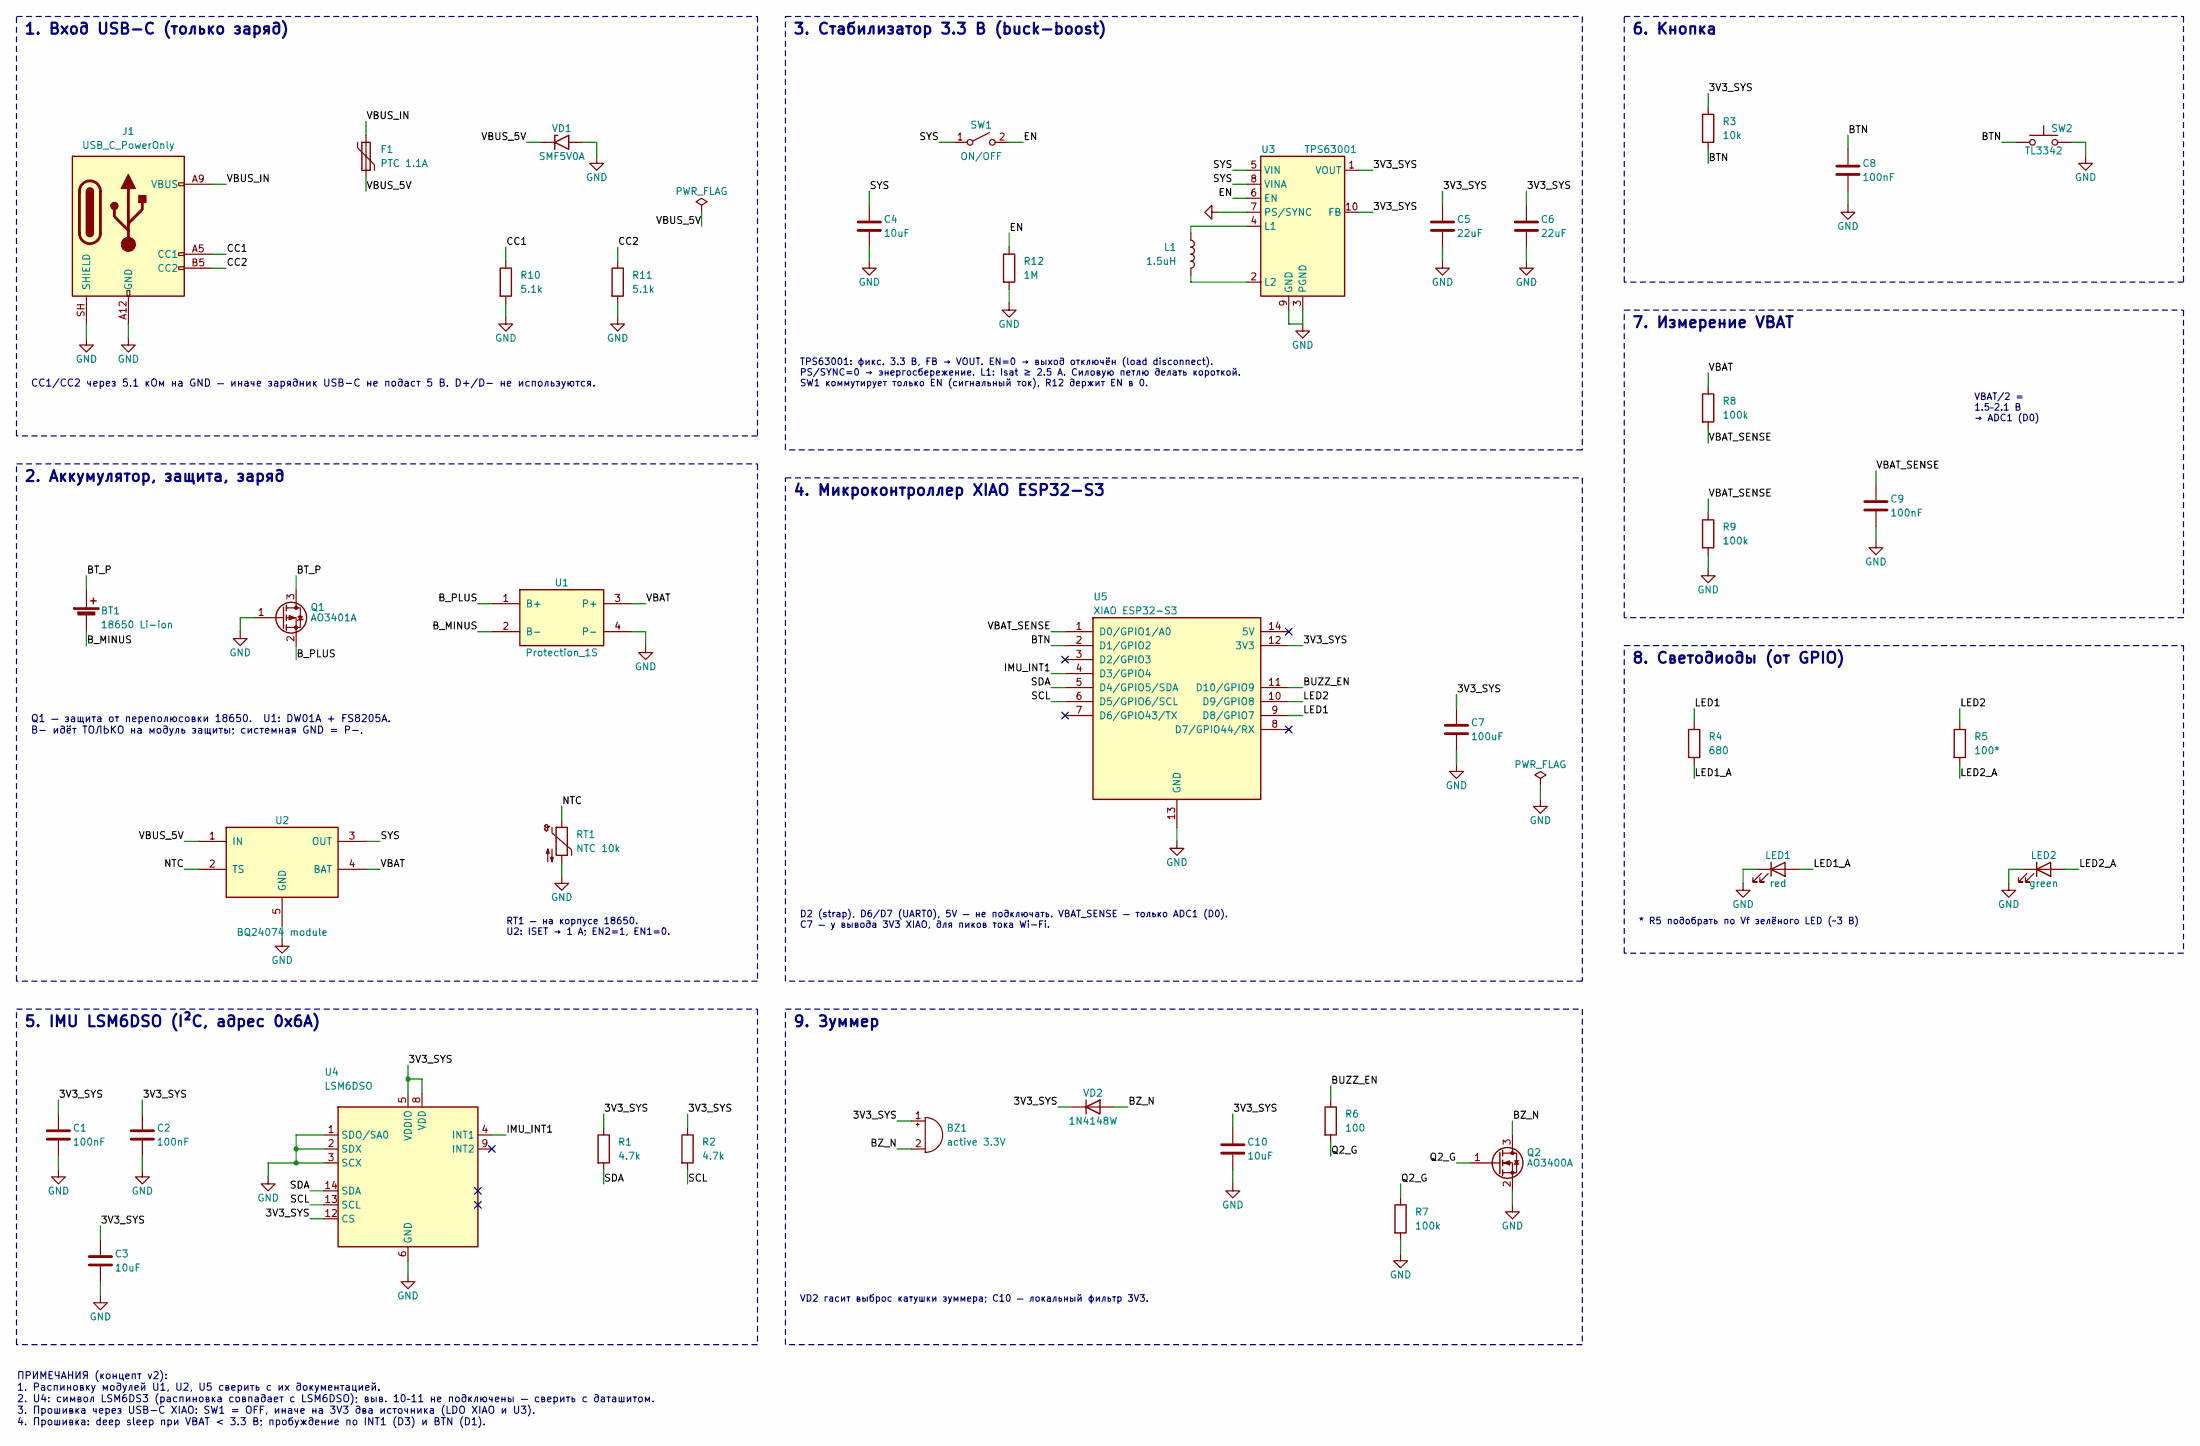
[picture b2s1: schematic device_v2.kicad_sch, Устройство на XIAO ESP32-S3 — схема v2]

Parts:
BT1: 18650 Li-ion; BatteryHolder_Keystone_1042_1x18650
BZ1: active 3.3V; Buzzer_12x9.5RM7.6
C1, C2, C8, C9: 100nF; C_0603_1608Metric
C3, C4, C10: 10uF; C_0805_2012Metric
C5, C6: 22uF; C_0805_2012Metric
C7: 100uF; C_1206_3216Metric
F1: PTC 1.1A; Fuse_1206_3216Metric
J1: USB_C_PowerOnly; USB_C_Receptacle_GCT_USB4125-xx-x_6P_TopMnt_Horizontal
L1: 1.5uH; L_Bourns-SRN4018
LED1: red; LED_0603_1608Metric
LED2: green; LED_0603_1608Metric
Q1: AO3401A; SOT-23
Q2: AO3400A; SOT-23
R1, R2: 4.7k; R_0603_1608Metric
R3: 10k; R_0603_1608Metric
R4: 680; R_0603_1608Metric
R5: 100*; R_0603_1608Metric
R6: 100; R_0603_1608Metric
R7, R8, R9: 100k; R_0603_1608Metric
R10, R11: 5.1k; R_0603_1608Metric
R12: 1M; R_0603_1608Metric
RT1: NTC 10k; NTC_WIRE_2P
SW1: ON/OFF; SW_SPDT_PCM12
SW2: TL3342; SW_SPST_TL3342
U1: Protection_1S; PROT_1S_HDR4
U2: BQ24074 module; BQ24074_MODULE_HDR5
U3: TPS63001; Texas_DRC0010J
U4: LSM6DSO; LGA-14_3x2.5mm_P0.5mm_LayoutBorder3x4y
U5: XIAO ESP32-S3; XIAO_ESP32S3_THT
VD1: SMF5V0A; D_SMF
VD2: 1N4148W; D_SOD-123

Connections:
/3V3_SYS: BZ1.1 (+), C1.1, C2.1, C3.1, C5.1, C6.1, C7.1, C10.1, R1.1, R2.1, R3.1, U3.1 (VOUT), U3.10 (FB), U4.5 (VDDIO), U4.8 (VDD), U4.12 (CS), U5.12 (3V3), VD2.1 (K)
/BTN: C8.1, R3.2, SW2.1, U5.2 (D1/GPIO2)
/BT_P: BT1.1 (+), Q1.3 (D)
/BUZZ_EN: R6.1, U5.11 (D10/GPIO9)
/BZ_N: BZ1.2 (-), Q2.3 (D), VD2.2 (A)
/B_MINUS: BT1.2 (-), U1.2 (B-)
/B_PLUS: Q1.2 (S), U1.1 (B+)
/CC1: J1.A5 (CC1), R10.1
/CC2: J1.B5 (CC2), R11.1
/EN: R12.1, SW1.2 (B), U3.6 (EN)
/IMU_INT1: U4.4 (INT1), U5.4 (D3/GPIO4)
/LED1: R4.1, U5.9 (D8/GPIO7)
/LED1_A: LED1.2 (A), R4.2
/LED2: R5.1, U5.10 (D9/GPIO8)
/LED2_A: LED2.2 (A), R5.2
/NTC: RT1.1, U2.2 (TS)
/Q2_G: Q2.1 (G), R6.2, R7.1
/SCL: R2.2, U4.13 (SCL), U5.6 (D5/GPIO6/SCL)
/SDA: R1.2, U4.14 (SDA), U5.5 (D4/GPIO5/SDA)
/SYS: C4.1, SW1.1 (A), U2.3 (OUT), U3.5 (VIN), U3.8 (VINA)
/VBAT: R8.1, U1.3 (P+), U2.4 (BAT)
/VBAT_SENSE: C9.1, R8.2, R9.1, U5.1 (D0/GPIO1/A0)
/VBUS_5V: F1.2, U2.1 (IN), VD1.1 (A1)
/VBUS_IN: F1.1, J1.A9 (VBUS), J1.B9 (VBUS)
GND: C1.2, C2.2, C3.2, C4.2, C5.2, C6.2, C7.2, C8.2, C9.2, C10.2, J1.A12 (GND), J1.B12 (GND), J1.SH (SHIELD), LED1.1 (K), LED2.1 (K), Q1.1 (G), Q2.2 (S), R7.2, R9.2, R10.2, R11.2, R12.2, RT1.2, SW2.2, U1.4 (P-), U2.5 (GND), U3.3 (PGND), U3.7 (PS/SYNC), U3.9 (GND), U3.11 (PGND), U4.1 (SDO/SA0), U4.2 (SDX), U4.3 (SCX), U4.6 (GND), U4.7 (GND), U5.13 (GND), VD1.2 (A2)
unnamed: L1.1, U3.4 (L1)
unnamed: L1.2, U3.2 (L2)

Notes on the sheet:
4. Микроконтроллер XIAO ESP32-S3
CC1/CC2 через 5.1 кОм на GND — иначе зарядник USB-C не подаст 5 В. D+/D− не используются.
6. Кнопка
TPS63001: фикс. 3.3 В, FB → VOUT. EN=0 → выход отключён (load disconnect). PS/SYNC=0 → энергосбережение. L1: Isat ≥ 2.5 А. Силовую петлю делать короткой. SW1 коммутирует только EN (сигнальный ток), R12 держит EN в 0.
7. Измерение VBAT
* R5 подобрать по Vf зелёного LED (~3 В)
VBAT/2 = 1.5–2.1 В → ADC1 (D0)
2. Аккумулятор, защита, заряд
8. Светодиоды (от GPIO)
RT1 — на корпусе 18650. U2: ISET → 1 А; EN2=1, EN1=0.
D2 (strap), D6/D7 (UART0), 5V — не подключать. VBAT_SENSE — только ADC1 (D0). C7 — у вывода 3V3 XIAO, для пиков тока Wi-Fi.
9. Зуммер
1. Вход USB-C (только заряд)
VD2 гасит выброс катушки зуммера; C10 — локальный фильтр 3V3.
Q1 — защита от переполюсовки 18650. U1: DW01A + FS8205A. B− идёт ТОЛЬКО на модуль защиты; системная GND = P−.
5. IMU LSM6DSO (I²C, адрес 0x6A)
3. Стабилизатор 3.3 В (buck-boost)
ПРИМЕЧАНИЯ (концепт v2): 1. Распиновку модулей U1, U2, U5 сверить с их документацией. 2. U4: символ LSM6DS3 (распиновка совпадает с LSM6DSO); выв. 10–11 не подключены — сверить с даташитом. 3. Прошивка через USB-C XIAO: SW1 = OFF, иначе на 3V3 два источника (LDO XIAO и U3). 4. Прошивка: deep sleep 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

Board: 2 copper layers, 41 parts (0 on the bottom side), 27 nets, no tracks yet.

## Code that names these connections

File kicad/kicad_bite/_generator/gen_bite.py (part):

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
CUSTOM = {}
xp = []
L_ = [('1', 'D0/GPIO1/A0'), ('2', 'D1/GPIO2'), ('3', 'D2/GPIO3'), ('4', 'D3/GPIO4'),
      ('5', 'D4/GPIO5/SDA'), ('6', 'D5/GPIO6/SCL'), ('7', 'D6/GPIO43/TX')]
for i, (n, nm) in enumerate(L_):
    xp.append(pin('bidirectional', -20.32, 12.7 - 2.54 * i, 0, nm, n))
xp.append(pin('power_in', 20.32, 12.7, 180, '5V', '14'))
xp.append(pin('power_in', 20.32, 10.16, 180, '3V3', '12'))
R_ = [('11', 'D10/GPIO9'), ('10', 'D9/GPIO8'), ('9', 'D8/GPIO7'), ('8', 'D7/GPIO44/RX')]
for i, (n, nm) in enumerate(R_):
    xp.append(pin('bidirectional', 20.32, 2.54 - 2.54 * i, 180, nm, n))
xp.append(pin('power_in', 0, -22.86, 90, 'GND', '13'))
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gnd(VD1.p('2'))
power('PWR_FLAG', mm(54), mm(19))
wire((mm(54), mm(19)), (mm(54), mm(20)))
label(mm(54), mm(20), 'VBUS_5V', (-1, 0))

U6 = Part('Battery_Management:BQ24074RGT', 'U6', 'BQ24074RGT', 26, 32)
lbl(U6.p('13'), 'VBUS_5V')
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frame(5, 47, 58, 78, '2. Аккумулятор 18650 и защита (DW01A + FS8205A)')
J2 = Part('Connector_Generic:Conn_01x04', 'J2', 'JST-PH 4P', 12, 57,
          fp='Connector_JST:JST_PH_B4B-PH-SM4-TB_1x04-1MP_P2.00mm_Vertical', fields='lib',
          desc='JST-PH 4-pin vertical SMD on the bottom side at the cap end: 18650 cell + NTC cable (PHR-4)')
lbl(J2.p('1'), 'BT_P')
lbl(J2.p('2'), 'B_MINUS')
lbl(J2.p('3'), 'NTC')
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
